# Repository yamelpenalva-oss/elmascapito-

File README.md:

# Robot Futbolista Autónomo

---

## Institución

Escuela de Educación Secundaria Técnica N° 5  
“2 de Abril” – Temperley – Buenos Aires

---

## Materia

Montajes de Proyectos Electrónicos

---

## Grupo

Taquito

---

## Autores

Nuñez, Ian — naikalo2000@gmail.com  
Guerra, Marcos — marcoscolegio3@gmail.com  
Penalva, Yamel — yamelpenalva@gmail.com  

---

## Profesor

Ing. Martín Leguizamón

---

## Descripción del proyecto

El presente proyecto consiste en el desarrollo de un robot futbolista autónomo, diseñado para participar en ligas nacionales de robótica.

El sistema integra hardware y software para permitir un comportamiento autónomo capaz de interactuar con el entorno en tiempo real, mediante la detección de la pelota, posicionamiento en el campo de juego y toma de decisiones.

El control del robot se realiza a través de microcontroladores ESP32 programados , aplicando principios de programación embebida.

---

## Objetivos

- Desarrollar un robot autónomo orientado a competencias de fútbol robótico  
- Integrar sensores, actuadores y microcontroladores  
- Implementar lógica de control en tiempo real  
- Aplicar conocimientos de electrónica y programación  
- Lograr un sistema funcional y eficiente  

---

## Materiales utilizados

- Motores de corriente continua (x4)  
- Módulo WiFi/Bluetooth  
- Microcontroladores ESP32 (x2)  
- Controladores de motor (TN6612 o TA6586)  

---

## Tecnologías y herramientas

- Lenguaje: C++ (framework Arduino / ESP32)  
- Entorno de desarrollo: Arduino IDE  
- Comunicación: WiFi y Bluetooth  
- Control de motores mediante PWM  
- Lectura de sensores digitales y analógicos  

---

## Lógica del sistema

El funcionamiento del robot se basa en una arquitectura de control que incluye:

- Lectura continua de sensores  
- Procesamiento de datos en tiempo real  
- Toma de decisiones mediante estructuras condicionales  
- Control de actuadores en función del entorno  

El comportamiento general contempla estrategias de búsqueda, ataque y corrección de trayectoria.

---

## Funcionamiento

El firmware desarrollado permite:

- Controlar el movimiento del robot  
- Procesar información del entorno  
- Ejecutar estrategias de juego  
- Adaptarse a condiciones variables durante la competencia  

El código se encuentra estructurado de forma modular, facilitando su mantenimiento y escalabilidad.

---

## Estado del proyecto

- Sistema funcional  
- Integración de hardware completa  
- Control de motores implementado  
- Proyecto en mejora continua  

---

## Mejoras futuras

- Optimización del sistema de detección de pelota  
- Mejora en la precisión de movimiento  
- Implementación de comunicación entre módulos  
- Desarrollo de estrategias más avanzadas  

---

## Enfoque de ingeniería

El proyecto fue desarrollado con un enfoque práctico, orientado a su implementación en entornos reales de competencia, priorizando:

- Robustez del sistema  
- Simplicidad en la lógica de control  
- Eficiencia en el uso de recursos  
- Claridad en la estructura del código  

---

## preguntas 

-Ante cualquier consulta o inconveniente, comuníquese con Yamel Penalva a través de Gmail.

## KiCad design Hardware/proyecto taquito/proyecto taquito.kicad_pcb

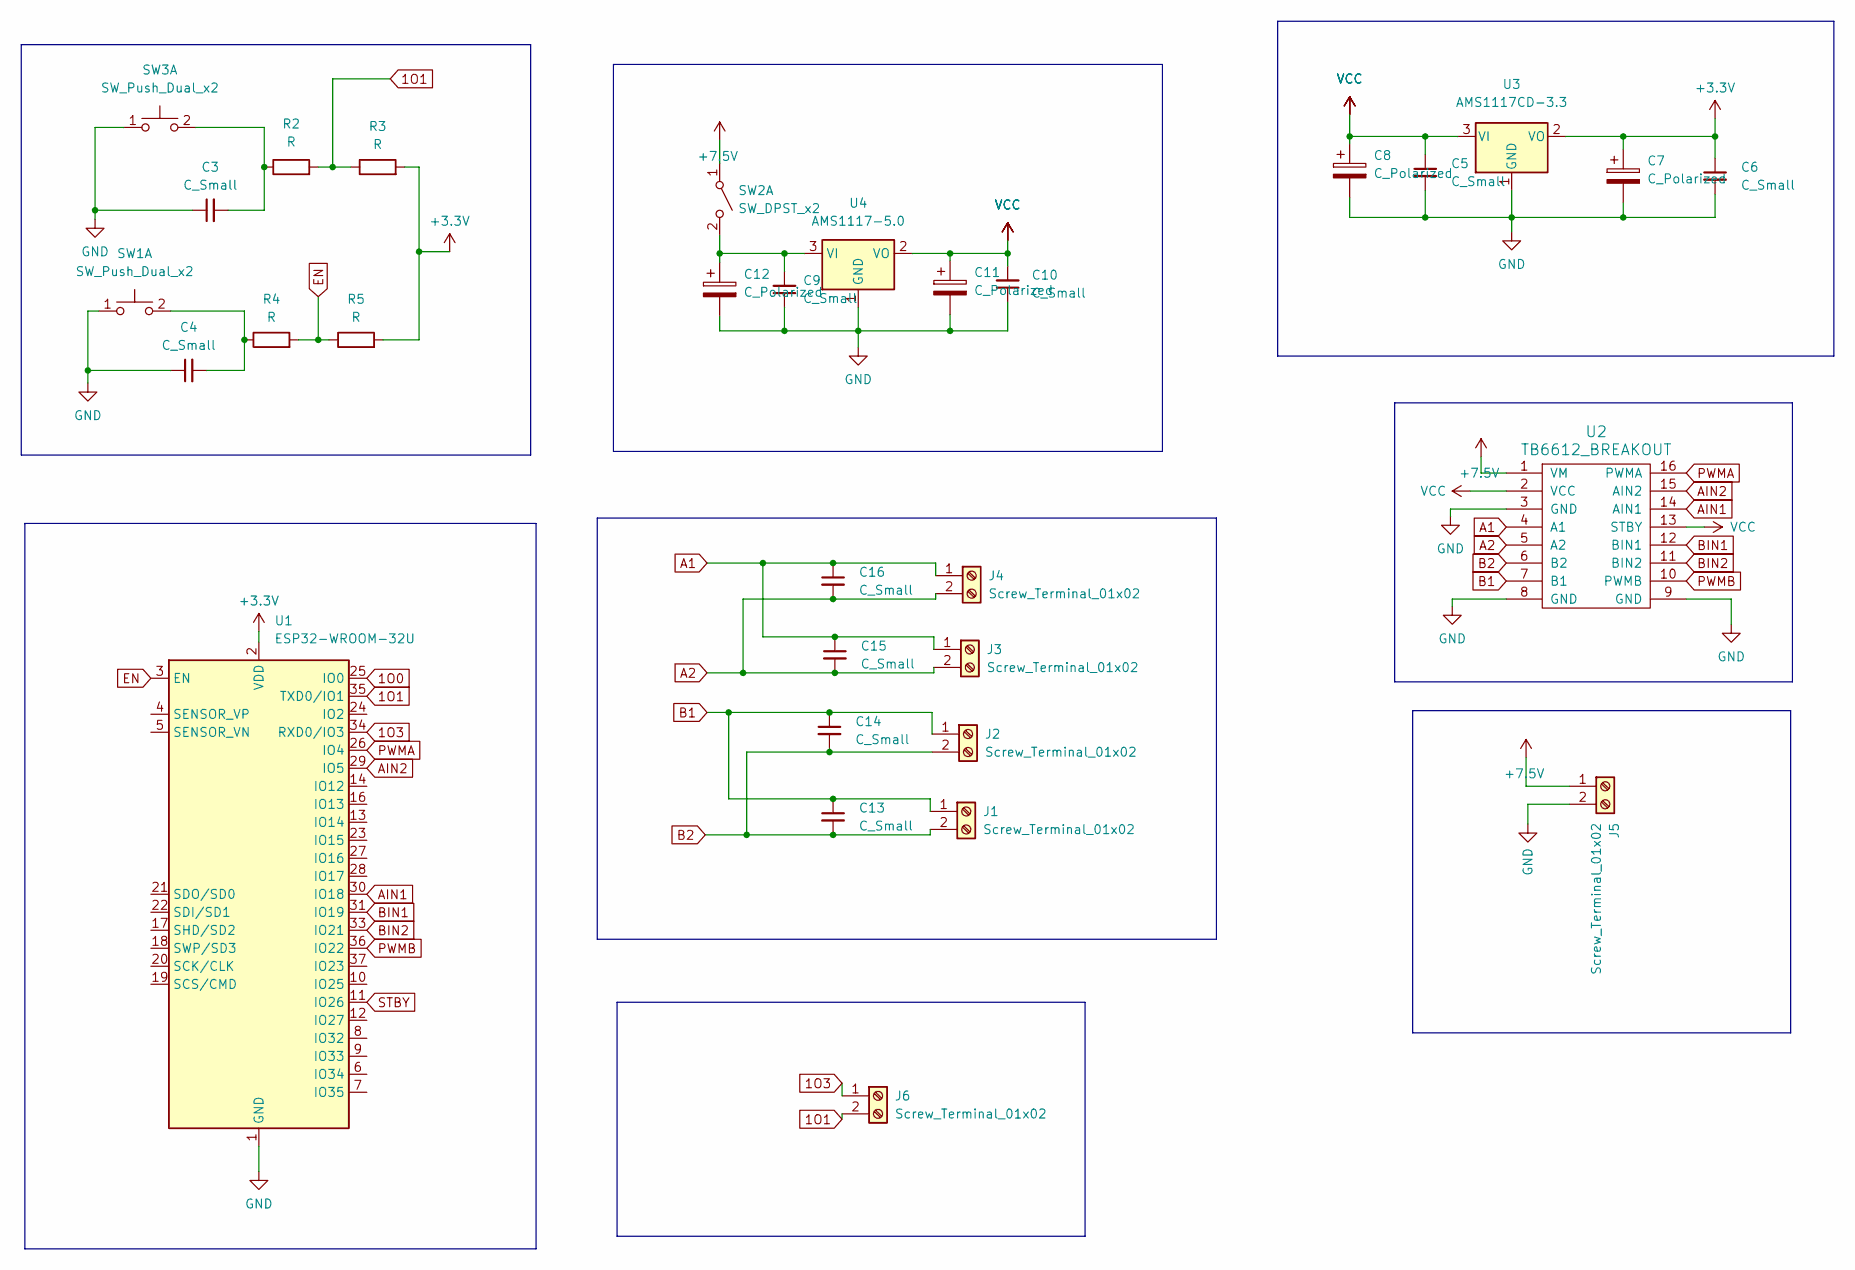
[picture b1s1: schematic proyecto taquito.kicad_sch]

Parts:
C3, C4, C5, C6, C9, C10: C_Small; R_0805_2012Metric_Pad1.20x1.40mm_HandSolder
C7, C8, C11, C12: C_Polarized; R_0805_2012Metric_Pad1.20x1.40mm_HandSolder
C13, C14, C15, C16: C_Small; C_Disc_D3.0mm_W1.6mm_P2.50mm
J1, J2, J3, J4, J5: Screw_Terminal_01x02; TerminalBlock_MaiXu_MX126-5.0-02P_1x02_P5.00mm
J6: Screw_Terminal_01x02; PinHeader_1x02_P2.54mm_Vertical
R2, R3, R4, R5: R; R_0805_2012Metric
SW1, SW3: SW_Push_Dual_x2; SW_PUSH_6mm
SW2: SW_DPST_x2; SW_ATE1D-2M3-10-Z
U1: ESP32-WROOM-32U
U2: TB6612_BREAKOUT; MODULE_ROB-14450
U3: AMS1117CD-3.3; SOT-223-3_TabPin2
U4: AMS1117-5.0; SOT-223-3_TabPin2

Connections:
1O0: U1.25 (IO0)
1O1: J6.2, R2.2, R3.1, U1.35 (TXD0/IO1)
1O3: J6.1, U1.34 (RXD0/IO3)
+3.3V: C6.1, C7.1, R3.2, R5.2, U1.2 (VDD), U3.2 (VO)
+7.5V: J5.1, SW2.1 (A), U2.1 (VM)
A1: C15.1, C16.1, J3.1, J4.1, U2.4 (A1)
A2: C15.2, C16.2, J3.2, J4.2, U2.5 (A2)
AIN1: U1.30 (IO18), U2.14 (AIN1)
AIN2: U1.29 (IO5), U2.15 (AIN2)
B1: C13.1, C14.1, J1.1, J2.1, U2.7 (B1)
B2: C13.2, C14.2, J1.2, J2.2, U2.6 (B2)
BIN1: U1.31 (IO19), U2.12 (BIN1)
BIN2: U1.33 (IO21), U2.11 (BIN2)
EN: R4.2, R5.1, U1.3 (EN)
GND: C3.1, C4.1, C5.2, C6.2, C7.2, C8.2, C9.1, C10.1, C11.2, C12.2, J5.2, SW1.1 (C), SW3.1 (C), U1.1 (GND), U1.15 (GND), U1.38 (GND), U1.39 (GND), U2.3 (GND), U2.8 (GND), U2.9 (GND), U3.1 (GND), U4.1 (GND)
unnamed: C4.2, R4.1, SW1.2 (D)
unnamed: C9.2, C12.1, SW2.2 (B), U4.3 (VI)
unnamed: C3.2, R2.1, SW3.2 (D)
PWMA: U1.26 (IO4), U2.16 (PWMA)
PWMB: U1.36 (IO22), U2.10 (PWMB)
STBY: U1.11 (IO26)
VCC: C5.1, C8.1, C10.2, C11.1, U2.2 (VCC), U2.13 (STBY), U3.3 (VI), U4.2 (VO)

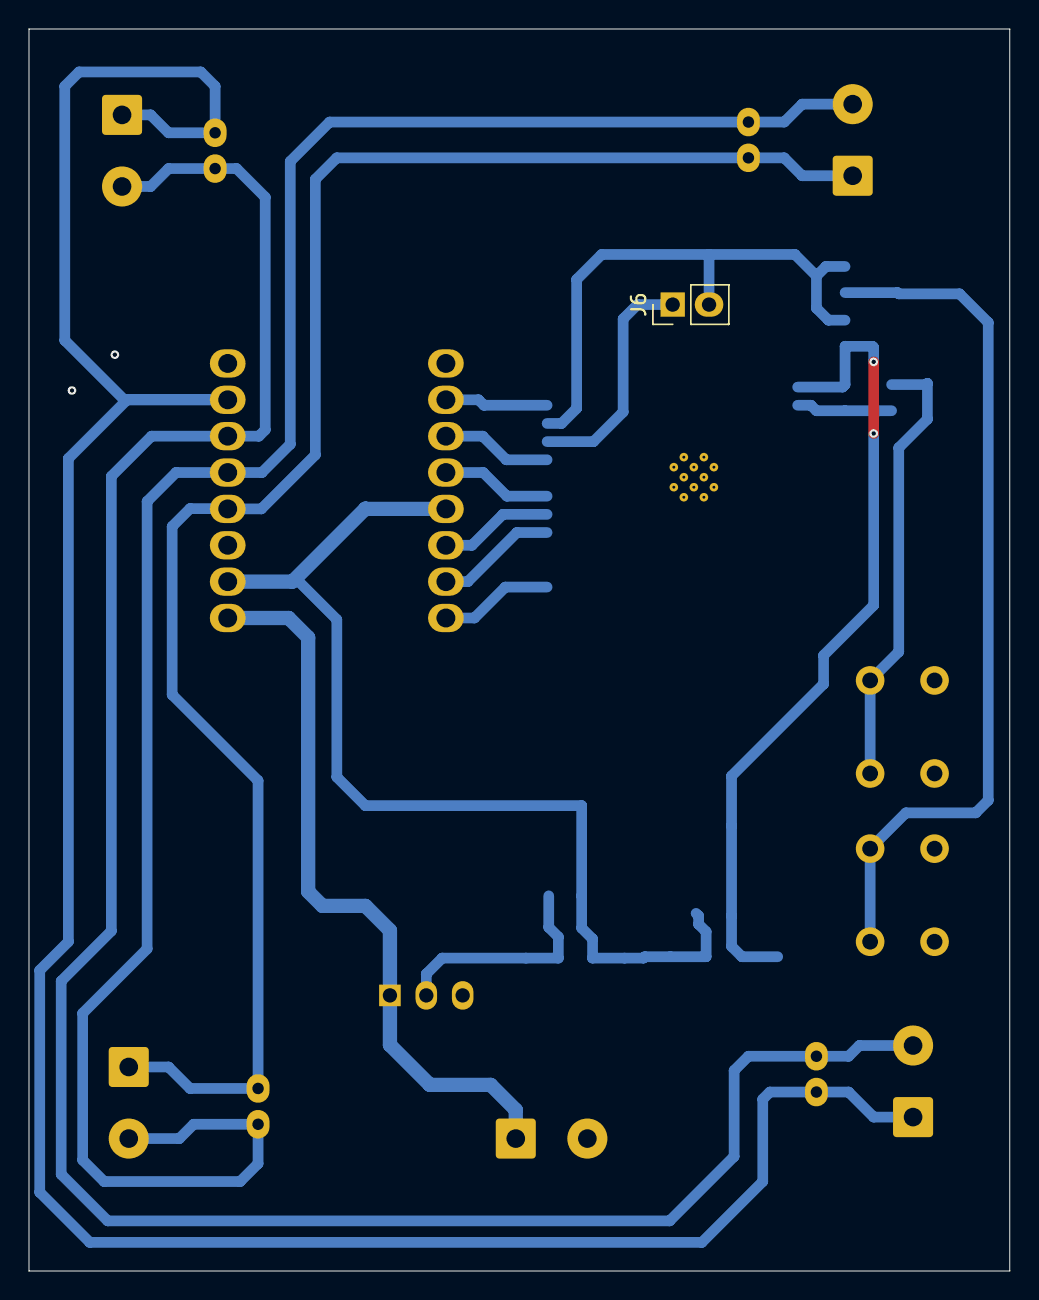
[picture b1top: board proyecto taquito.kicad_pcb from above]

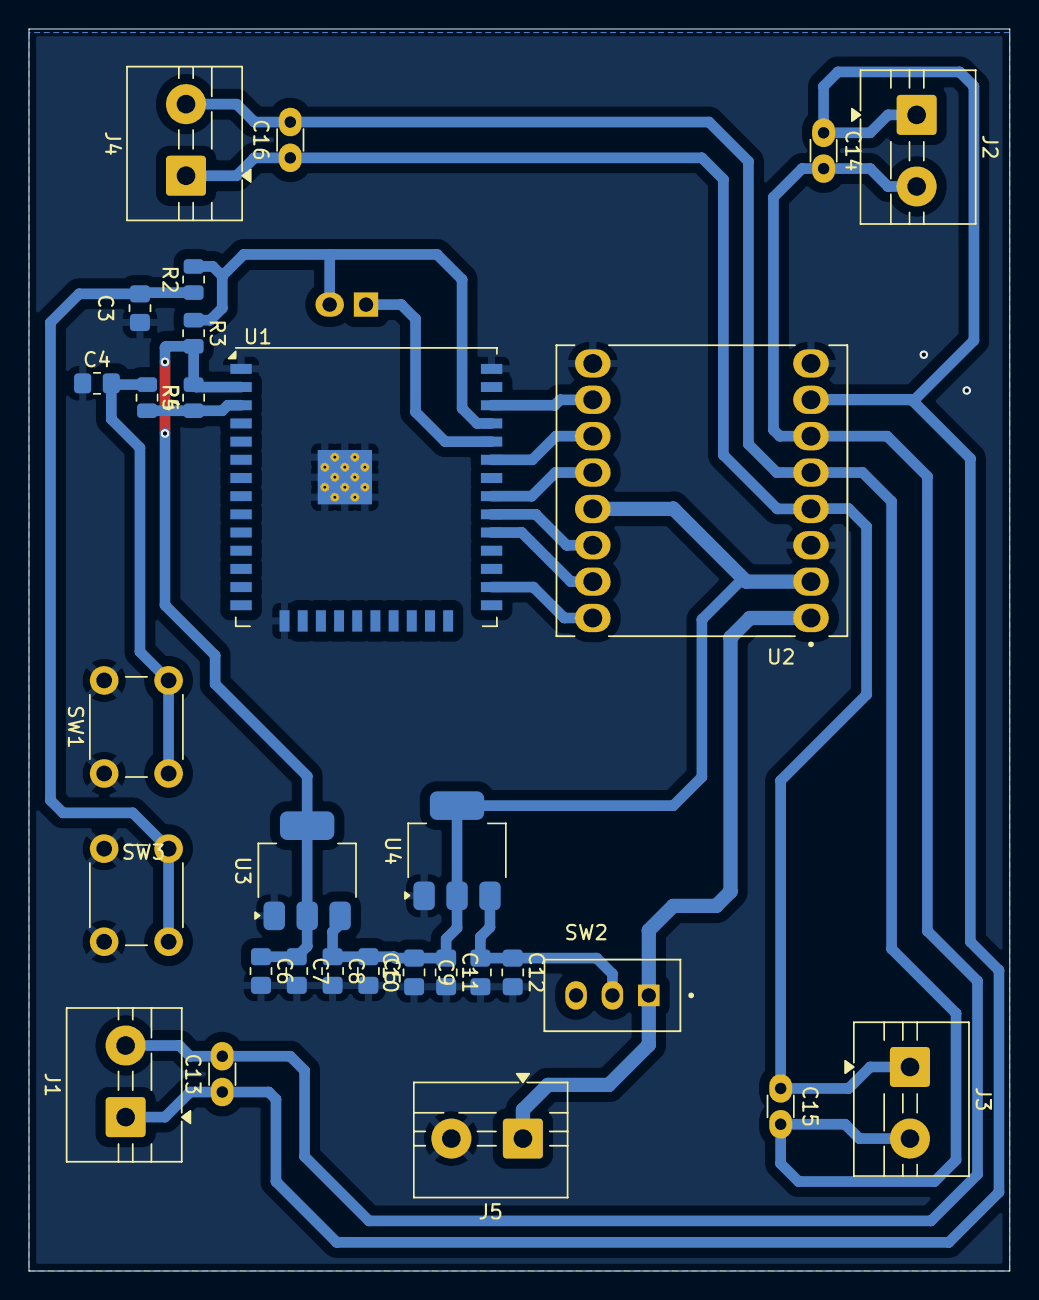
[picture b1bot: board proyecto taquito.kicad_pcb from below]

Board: 2 copper layers, 68.5 x 86.8 mm, 31 parts (30 on the bottom side), 20 nets.

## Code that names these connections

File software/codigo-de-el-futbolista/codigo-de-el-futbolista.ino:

#include <Ps3Controller.h>


const int PIN_AIN1 = 18;
const int PIN_PWMA = 4;
const int PIN_AIN2 = 5;
const int PIN_BIN1 = 19;
const int PIN_BIN2 = 21;
const int PIN_PWMB = 22;

const int PWM_FREQ        = 5000;  
const int PWM_RESOLUTION  = 8;      
const int CH_PWMA         = 0;      
const int CH_PWMB         = 1;      

const int DEADZONE        = 15;     
const int VEL_NORMAL_MAX  = 180;   
const int VEL_TURBO_MAX   = 255;    
const int VEL_CRUCETA     = 200;    


bool turboActivo   = false;
bool paroEmergencia = false;
bool ultimoEstadoCross = false; 
bool ultimoEstadoCircle = false; 
void motorA(int vel) {
  vel = constrain(vel, -255, 255);
  if (vel > 0) {
    digitalWrite(PIN_AIN1, HIGH);
    digitalWrite(PIN_AIN2, LOW);
  } else if (vel < 0) {
    digitalWrite(PIN_AIN1, LOW);
    digitalWrite(PIN_AIN2, HIGH);
  } else {
    digitalWrite(PIN_AIN1, LOW);
    digitalWrite(PIN_AIN2, LOW);
  }
  ledcWrite(CH_PWMA, abs(vel));
}


void motorB(int vel) {
  vel = constrain(vel, -255, 255);
  if (vel > 0) {
    digitalWrite(PIN_BIN1, HIGH);
    digitalWrite(PIN_BIN2, LOW);
  } else if (vel < 0) {
    digitalWrite(PIN_BIN1, LOW);
    digitalWrite(PIN_BIN2, HIGH);
  } else {
    digitalWrite(PIN_BIN1, LOW);
    digitalWrite(PIN_BIN2, LOW);
  }
  ledcWrite(CH_PWMB, abs(vel));
}


void detenerMotores() {
  digitalWrite(PIN_AIN1, LOW);
  digitalWrite(PIN_AIN2, LOW);
  digitalWrite(PIN_BIN1, LOW);
  digitalWrite(PIN_BIN2, LOW);
  ledcWrite(CH_PWMA, 0);
  ledcWrite(CH_PWMB, 0);
}

void driverEnable(bool habilitado) {
  digitalWrite(PIN_STBY, habilitado ? HIGH : LOW);
}


void aplicarZonaMuerta(int &valor) {
  if (abs(valor) < DEADZONE) valor = 0;
}

void manejarConStick() {
  
  int ejeY = -Ps3.data.analog.stick.ly; 
  int ejeX =  Ps3.data.analog.stick.lx; 

  aplicarZonaMuerta(ejeY);
  aplicarZonaMuerta(ejeX);

  if (ejeY == 0 && ejeX == 0) {
    detenerMotores();
    return;
  }

  int velMax = turboActivo ? VEL_TURBO_MAX : VEL_NORMAL_MAX;

  
  int velIzq = ejeY + ejeX;
  int velDer = ejeY - ejeX;

  
  velIzq = map(constrain(velIzq, -128, 127), -128, 127, -velMax, velMax);
  velDer = map(constrain(velDer, -128, 127), -128, 127, -velMax, velMax);

  motorA(velIzq); 
  motorB(velDer); 
}

void manejarConCruceta() {
  int velMax = turboActivo ? VEL_TURBO_MAX : VEL_CRUCETA;

  bool arriba   = Ps3.data.button.up;
  bool abajo    = Ps3.data.button.down;
  bool izquierda = Ps3.data.button.left;
  bool derecha  = Ps3.data.button.right;

  if (arriba && izquierda) {
    motorA(velMax / 3);
    motorB(velMax);
  } else if (arriba && derecha) {
    motorA(velMax);
    motorB(velMax / 3);
  } else if (abajo && izquierda) {
    motorA(-velMax / 3);
    motorB(-velMax);
  } else if (abajo && derecha) {
    motorA(-velMax);
    motorB(-velMax / 3);
  } else if (arriba) {
    motorA(velMax);
    motorB(velMax);
  } else if (abajo) {
    motorA(-velMax);
    motorB(-velMax);
  } else if (izquierda) {
    motorA(-velMax);
    motorB(velMax);
  } else if (derecha) {
    motorA(velMax);
    motorB(-velMax);
  } else {
    detenerMotores();
  }
}

bool stickActivo() {
  int ejeY = Ps3.data.analog.stick.ly;
  int ejeX = Ps3.data.analog.stick.lx;
  return (abs(ejeY) >= DEADZONE) || (abs(ejeX) >= DEADZONE);
}

bool crucetaActiva() {
  return Ps3.data.button.up || Ps3.data.button.down ||
         Ps3.data.button.left || Ps3.data.button.right;
}

void manejarBotonesEspeciales() {

  bool crossAhora = Ps3.data.button.cross;
  if (crossAhora && !ultimoEstadoCross) {
    turboActivo = !turboActivo;
    Serial.print("Turbo: ");
    Serial.println(turboActivo ? "ACTIVADO" : "desactivado");
  }
  ultimoEstadoCross = crossAhora;

  bool circleAhora = Ps3.data.button.circle;
  if (circleAhora && !ultimoEstadoCircle) {
    paroEmergencia = !paroEmergencia;
    Serial.print("Paro de emergencia: ");
    Serial.println(paroEmergencia ? "ACTIVADO (motores bloqueados)" : "liberado");
    if (paroEmergencia) {
      detenerMotores();
    }
  }
  ultimoEstadoCircle = circleAhora;
}

void onPs3Notify() {
  manejarBotonesEspeciales();

  if (paroEmergencia) {
    detenerMotores();
    return;
  }

  if (stickActivo()) {
    manejarConStick();
  } else if (crucetaActiva()) {
    manejarConCruceta();
  } else {
    detenerMotores();
  }
}

void onPs3Connect() {
  Serial.println(">> Mando PS3 CONECTADO");
  driverEnable(true);
  detenerMotores();
}

void onPs3Disconnect() {
  Serial.println(">> Mando PS3 DESCONECTADO - deteniendo motores por seguridad");
  detenerMotores();
  driverEnable(false);
}

void setup() {
  Serial.begin(115200);
  delay(300);

  pinMode(PIN_AIN1, OUTPUT);
  pinMode(PIN_AIN2, OUTPUT);
  pinMode(PIN_BIN1, OUTPUT);
  pinMode(PIN_BIN2, OUTPUT);
  

  ledcSetup(CH_PWMA, PWM_FREQ, PWM_RESOLUTION);
  ledcAttachPin(PIN_PWMA, CH_PWMA);
  ledcSetup(CH_PWMB, PWM_FREQ, PWM_RESOLUTION);
  ledcAttachPin(PIN_PWMB, CH_PWMB);

  driverEnable(false); 
  detenerMotores();

  Ps3.attach(onPs3Notify);
  Ps3.attachOnConnect(onPs3Connect);
  Ps3.attachOnDisconnect(onPs3Disconnect);
  Ps3.begin();

}

void loop() {
  if (!Ps3.isConnected()) {
    detenerMotores();
  }
  delay(20);
}
